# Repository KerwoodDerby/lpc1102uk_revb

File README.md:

# lpc1102uk_revb

## A slight improvement on richardeoin's OSHPark design.
That design can be found [here](https://oshpark.com/shared_projects/Tokc44bz).

##My revision

I wanted access to the interior pins, so I tweaked the WLCSP16 pattern to give me a little room
for a 5 mil trace. This exceeds the design rules for OSHPark 2-layer boards, but I can claim
success, having just gotten my [boards](https://oshpark.com/shared_projects/Yf2WkhM2) back and
successfully programmed my diminutive LPC1102UK!

Only the XTALIN pin is not brought out, since I thought that wasn't critical for doing
exploratory programming. I made other changes, mostly the size of the other LEDs and resistors.

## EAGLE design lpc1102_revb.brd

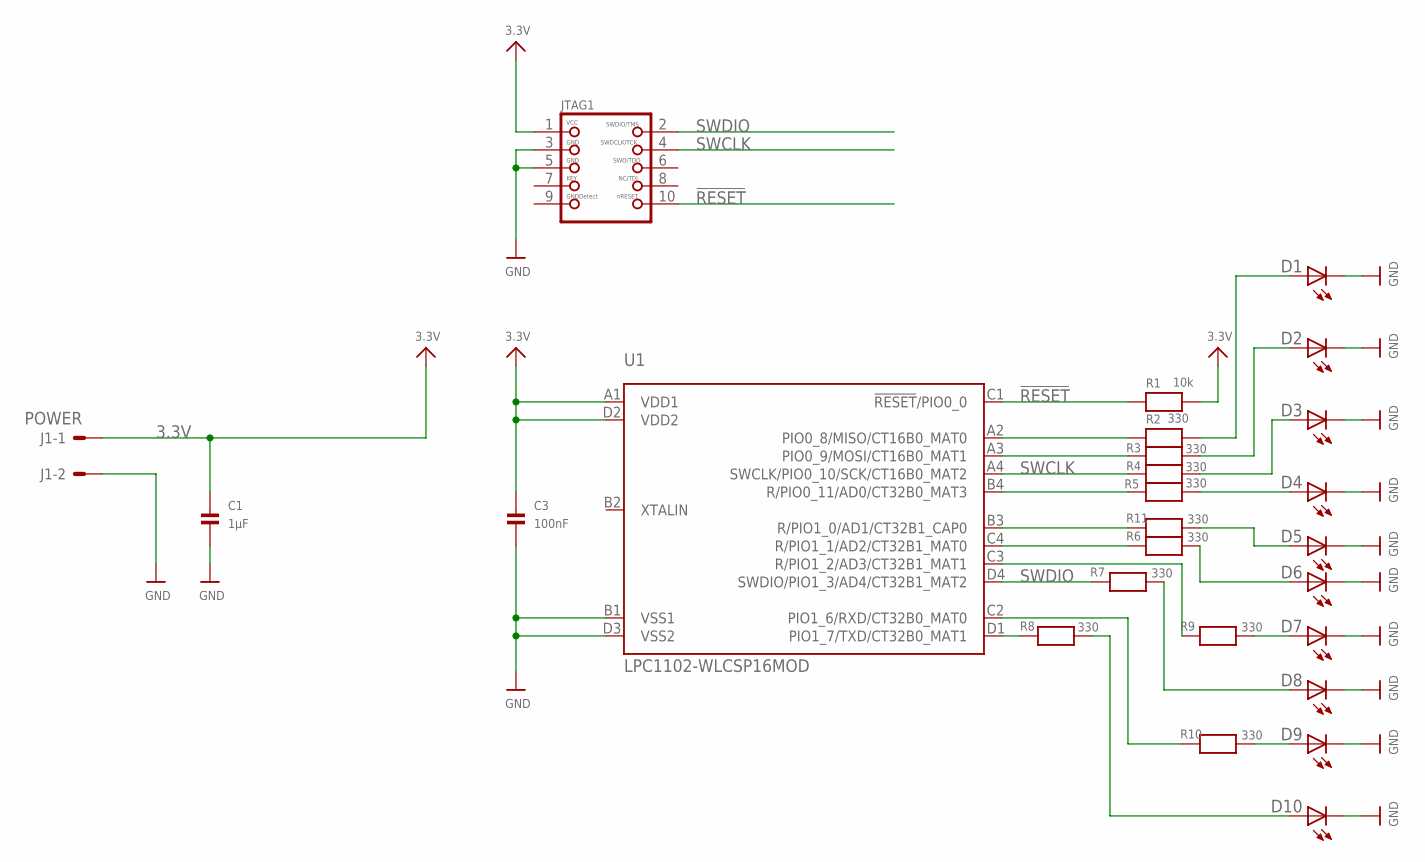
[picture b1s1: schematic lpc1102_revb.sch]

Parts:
C1: 1µF; _0402
C3: 100nF; _0402
D1, D2, D3, D4, D5, D6, D7, D8, D9, D10: LEDCHIP-LED0603; CHIP-LED0603
J1: POWER; 6410-02
JTAG1: JTAG-CORTEXM3SMT; 2X05_1.27MM_SMT
R1: 10k; _0402
R2, R3, R4, R5, R6, R7, R8, R9, R10, R11: 330; _0402
U1: LPC1102-WLCSP16MOD; WLCSP16_MOD

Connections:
3.3V: C1.1, C3.1, J1.1, JTAG1.1, R1.2, U1.A1 (VDD1), U1.D2 (VDD2)
!RESET: JTAG1.10, R1.1, U1.C1 (!RESET!/PIO0_0)
GND: C1.2, C3.2, D1.C, D2.C, D3.C, D4.C, D5.C, D6.C, D7.C, D8.C, D9.C, D10.C, J1.2, JTAG1.3, JTAG1.5, U1.B1 (VSS1), U1.D3 (VSS2)
unnamed: R8.1, U1.D1 (PIO1_7/TXD/CT32B0_MAT1)
unnamed: D1.A, R2.2
unnamed: R6.1, U1.C4 (R/PIO1_1/AD2/CT32B1_MAT0)
unnamed: R5.1, U1.B4 (R/PIO0_11/AD0/CT32B0_MAT3)
unnamed: D5.A, R11.2
unnamed: R3.1, U1.A3 (PIO0_9/MOSI/CT16B0_MAT1)
unnamed: R2.1, U1.A2 (PIO0_8/MISO/CT16B0_MAT0)
unnamed: R9.1, U1.C3 (R/PIO1_2/AD3/CT32B1_MAT1)
unnamed: D7.A, R9.2
unnamed: R10.1, U1.C2 (PIO1_6/RXD/CT32B0_MAT0)
unnamed: D9.A, R10.2
unnamed: R11.1, U1.B3 (R/PIO1_0/AD1/CT32B1_CAP0)
unnamed: D2.A, R3.2
unnamed: D3.A, R4.2
unnamed: D4.A, R5.2
unnamed: D6.A, R6.2
unnamed: D8.A, R7.2
unnamed: D10.A, R8.2
SWCLK: JTAG1.4, R4.1, U1.A4 (SWCLK/PIO0_10/SCK/CT16B0_MAT2)
SWDIO: JTAG1.2, R7.1, U1.D4 (SWDIO/PIO1_3/AD4/CT32B1_MAT2)

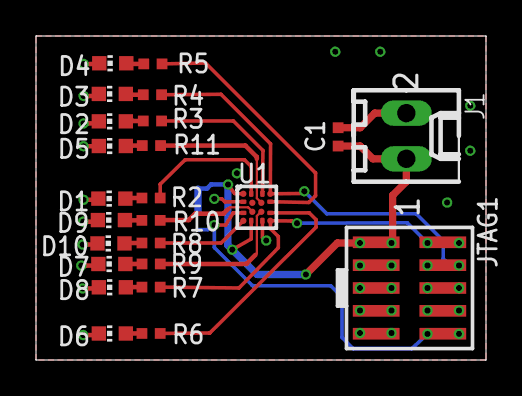
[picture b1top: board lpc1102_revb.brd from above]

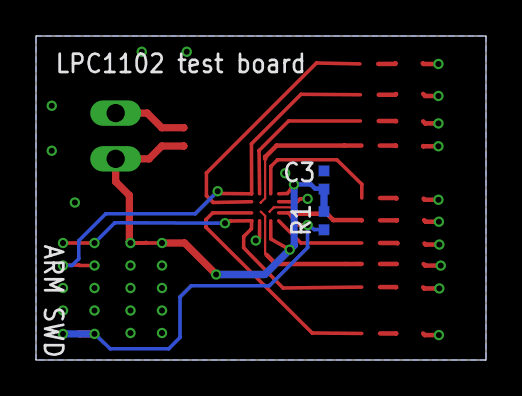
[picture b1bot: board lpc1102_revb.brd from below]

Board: 2 copper layers, 25.0 x 18.0 mm, 26 parts (2 on the bottom side), 23 nets.

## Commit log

2016-04-29 Added files via upload
    Initial commit
2016-04-29 Added a photo of the working board
2016-04-29 Modified README.md

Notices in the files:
parts and their libraries:
microbuilder_v3: This work is placed in the public domain, and may be freely used for commercial and non-commercial work with the following conditions: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
